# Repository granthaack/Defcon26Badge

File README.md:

# Defcon26Badge

************************************************
Read the wiki!
https://github.com/granthaack/Defcon26Badge/wiki
************************************************

This is a custom badge for our friend group. At its core, it's an Atmel ATMEGA328P running the arduino bootloader. 

Peripherals:

-5x10 RGB Neopixel array

-LISDH Triple Axis Accelerometer

-NRF24L01 2.4GHz wireless transciever

-Piezo Buzzer

-6 Tact Switches

-3 Status Lights

-UART Debugging Port

The chip is soldered to the board, so it's programmed using an Arduino as an ISP. This also enables easy access to UART.

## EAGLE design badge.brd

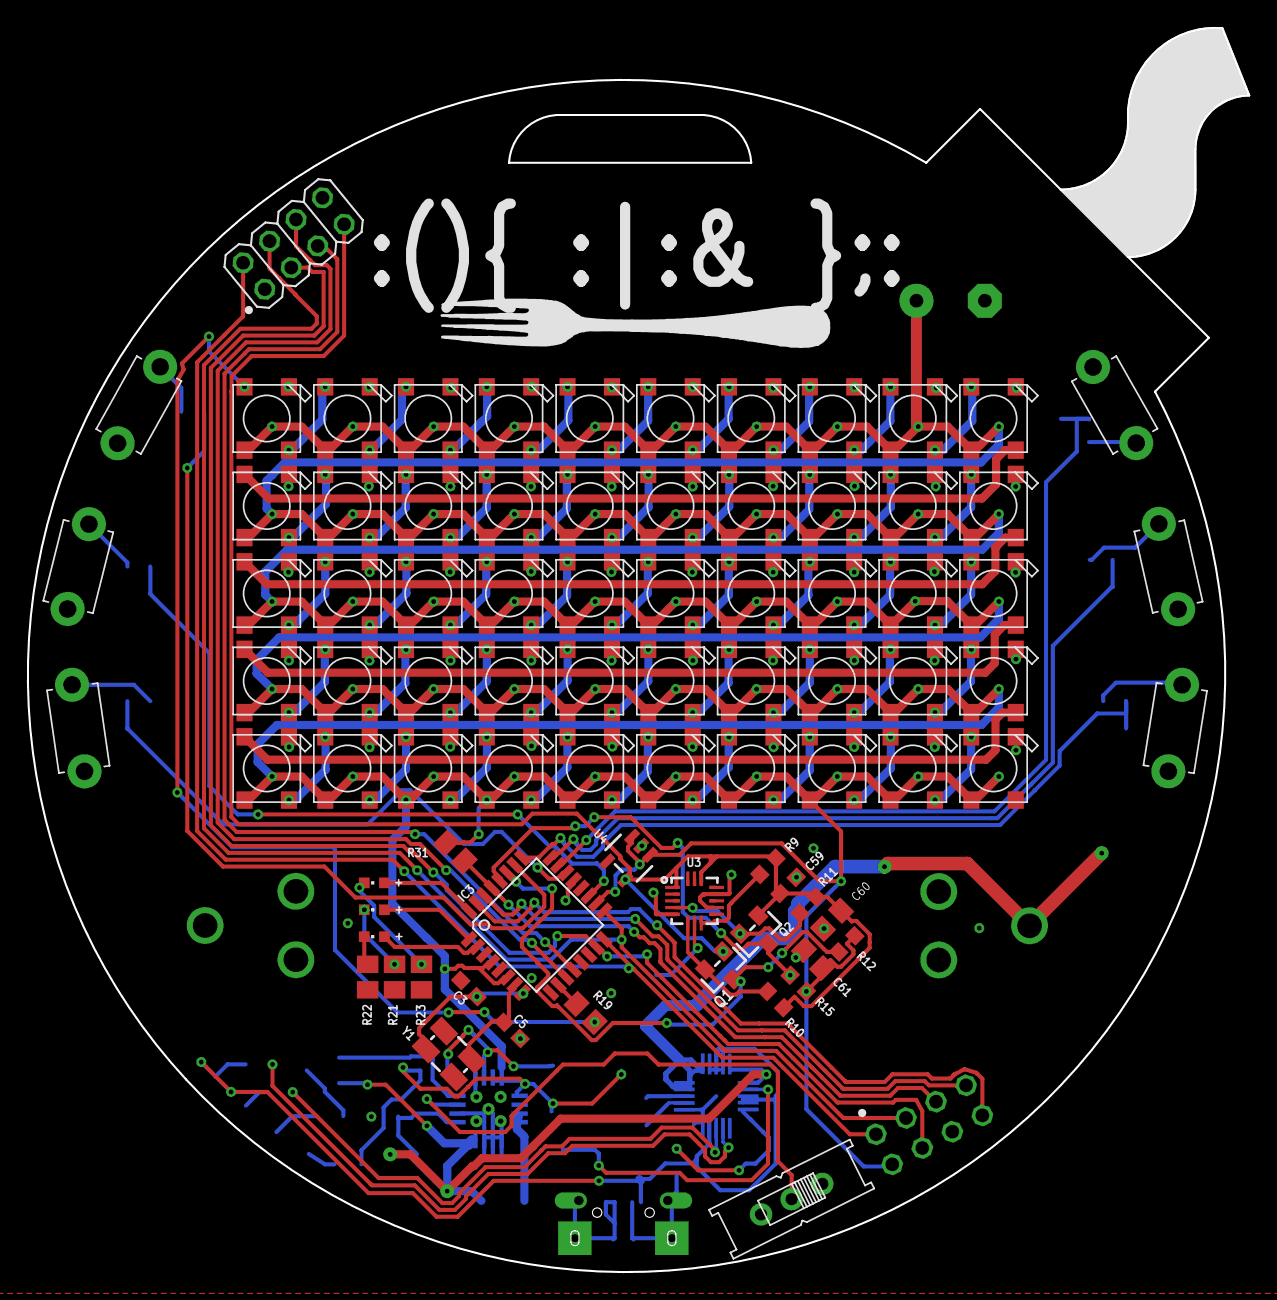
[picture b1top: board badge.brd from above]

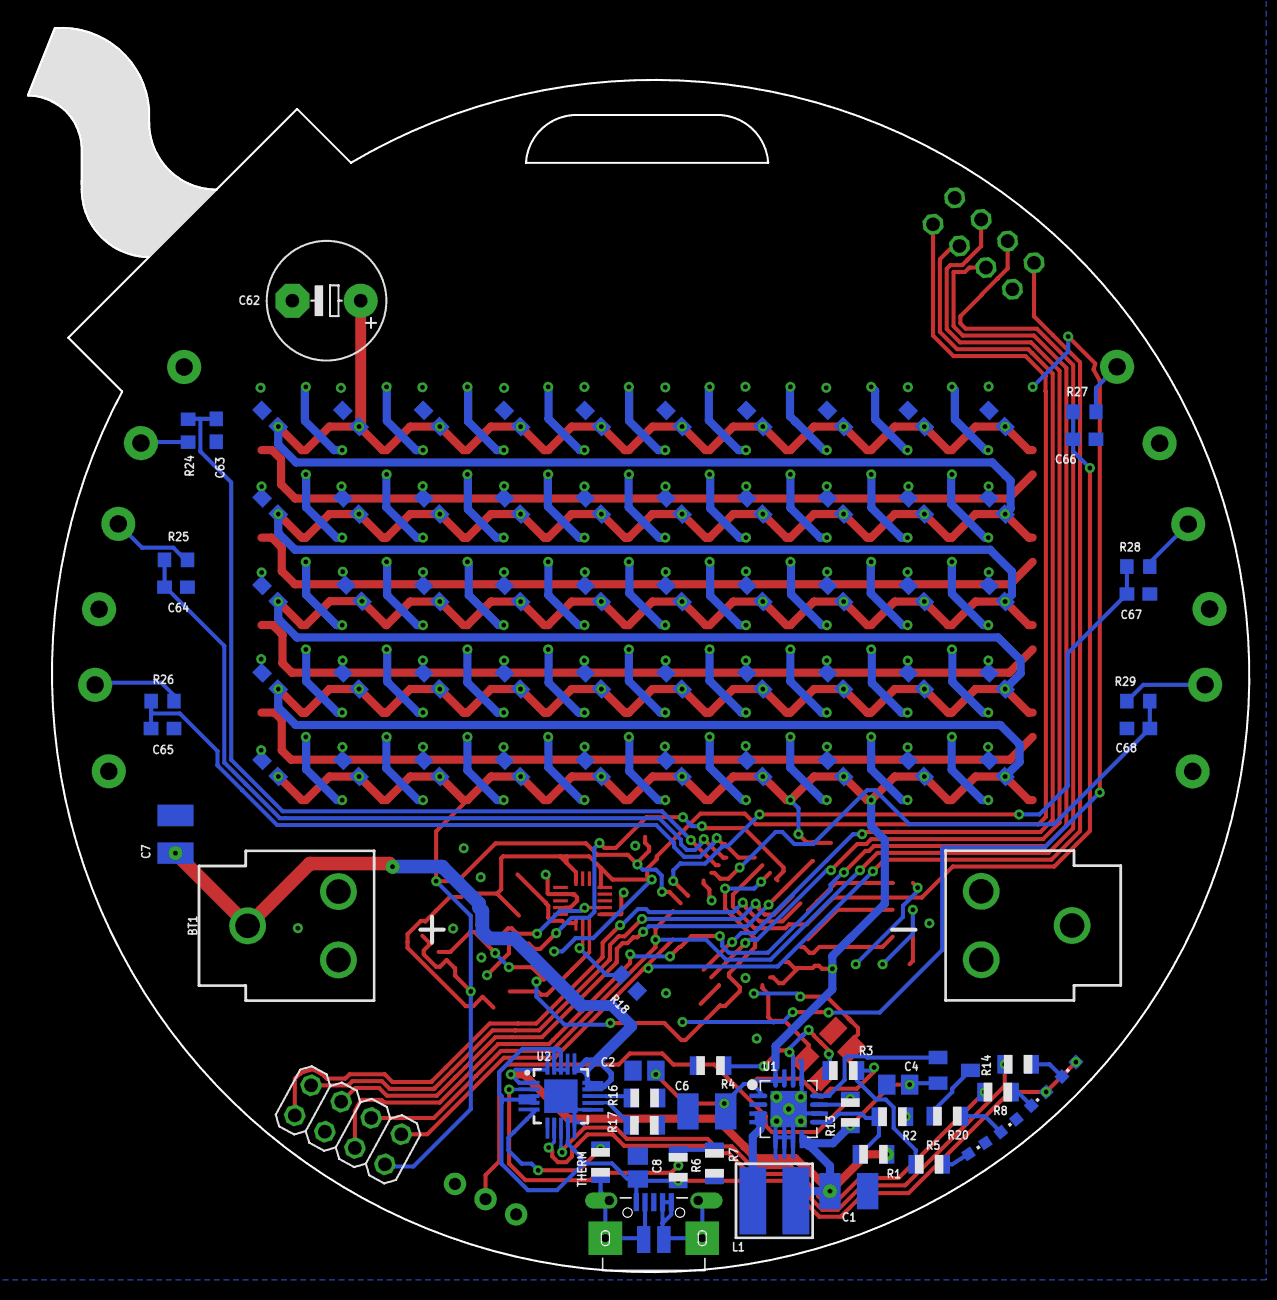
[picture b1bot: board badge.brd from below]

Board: 2 copper layers, 90.7 x 92.4 mm, 177 parts (95 on the bottom side), 107 nets.

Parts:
BT1: BATTERY_18650-HOLDER
C1, C7: 10uF; C1210
C2: 2.2uF; C0805
C3, C5: 22pF; C0603
C4: 0.1uF; C0805
C6: 100uF; C1210
C8: 10uf; C0805
C9, C10, C11, C12, C13, C14, C15, C16, C17, C18, C19, C20, C21, C22, C23, C24, C25, C26, C27, C28, C29, C30, C31, C32, C33, C34, C35, C36, C37, C38, C39, C40, C41, C42, C43, C44, C45, C46, C47, C48, C49, C50, C51, C52, C53, C54, C55, C56, C57, C58, C63, C64, C65, C66, C67, C68: 100nF; C0603
C59: 0.1uF; C0603
C60, C61: 10µF; C0805
C62: 1F; E5-8,5
CHRG/LBO: ORANGE; ADAFRUIT_CHIPLED_0603
CN4: MicroUSB; 4UCONN_20329
DONE: GREEN; ADAFRUIT_CHIPLED_0603
IC3: MEGA8-AI; TQFP32-08
JP1: PROG_HEADER; 2X04
JP3: TCVR_HEADER; 2X04
L1: 6.8uH; INDUCTOR_5X5MM_TDK_VLC5045
LBO: RED; ADAFRUIT_CHIPLED_0603
LED1, LED2, LED3, LED4, LED5, LED6, LED7, LED8, LED9, LED10, LED11, LED12, LED13, LED14, LED15, LED16, LED17, LED18, LED19, LED20, LED21, LED22, LED23, LED24, LED25, LED26, LED27, LED28, LED29, LED30, LED31, LED32, LED33, LED34, LED35, LED36, LED37, LED38, LED39, LED40, LED41, LED42, LED43, LED44, LED45, LED46, LED47, LED48, LED49, LED50: WS2812B5050-NARROW; WS2812B-NARROW
ON: BLUE; ADAFRUIT_CHIPLED_0603
Q1, Q2: BSS138; SOT23-WIDE
R1, R3: 1.87M; R0805
R2: 340K; R0805
R4, R13: 200K; R0805
R5, R8, R14, R20: 1K; R0805
R6: 270K; R0805
R7, R17: 100K; R0805
R9, R10, R11, R12, R15, R18: 10K; R0603
R16: 1.0K; R0805
R19: 470; R0805
R21, R22, R23: 220; M0805
R24, R25, R26, R27, R28, R29: 1k; R0603
R31: 10k; M0805
S1: EG1218
STAT1, STAT2, STAT3: GREEN; ADAFRUIT_CHIPLED_0603
SW1, SW2, SW3, SW4, SW5, SW6: TACT_PANA-EVQ
T1: MMUN2133LT1G; TRANSISTOR_SC59-BEC
THERM: 15K; R0805
U1: TPS61090RSAR; PVQFN-16
U2: MCP73871; QFN20_4MM
U3: LIS3DHTR; LGA16_3X3MM
U4: MIC5225-3.3; SOT23-5
Y1: 16.00MHz; CRYSTAL-SMD-3.2X2.5MM

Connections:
3.3V: C59.1, C60.1, JP3.7, Q1.1, Q2.1, R9.1, R10.2, R11.2, U3.1, U3.14, U4.5
+5V: C2.1, C6.1, C9.1, C10.1, C11.1, C12.1, C13.1, C14.1, C15.1, C16.1, C17.1, C18.1, C19.1, C20.1, C21.1, C22.1, C23.1, C24.1, C25.1, C26.1, C27.1, C28.1, C29.1, C30.1, C31.1, C32.1, C33.1, C34.1, C35.1, C36.1, C37.1, C38.1, C39.1, C40.1, C41.1, C42.1, C43.1, C44.1, C45.1, C46.1, C47.1, C48.1, C49.1, C50.1, C51.1, C52.1, C53.1, C54.1, C55.1, C56.1, C57.1, C58.1, C61.1, C62.+, IC3.4, IC3.6, IC3.18, JP1.2, LED1.1-VDD, LED2.1-VDD, LED3.1-VDD, LED4.1-VDD, LED5.1-VDD, LED6.1-VDD, LED7.1-VDD, LED8.1-VDD, LED9.1-VDD, LED10.1-VDD, LED11.1-VDD, LED12.1-VDD, LED13.1-VDD, LED14.1-VDD, LED15.1-VDD, LED16.1-VDD, LED17.1-VDD, LED18.1-VDD, LED19.1-VDD, LED20.1-VDD, LED21.1-VDD, LED22.1-VDD, LED23.1-VDD, LED24.1-VDD, LED25.1-VDD, LED26.1-VDD, LED27.1-VDD, LED28.1-VDD, LED29.1-VDD, LED30.1-VDD, LED31.1-VDD, LED32.1-VDD, LED33.1-VDD, LED34.1-VDD, LED35.1-VDD, LED36.1-VDD, LED37.1-VDD, LED38.1-VDD, LED39.1-VDD, LED40.1-VDD, LED41.1-VDD, LED42.1-VDD, LED43.1-VDD, LED44.1-VDD, LED45.1-VDD, LED46.1-VDD, LED47.1-VDD, LED48.1-VDD, LED49.1-VDD, LED50.1-VDD, R3.2, R5.1, R12.2, R15.2, R31.2, U1.1, U1.15, U1.16, U4.1, U4.3
BOOST_ENABLE: R13.2, S1.P, U1.11
CE: IC3.11, JP3.6
CSN: IC3.12, JP3.5
GND: BT1.GND@1, C1.2, C2.2, C3.2, C4.2, C5.2, C6.2, C7.2, C8.2, C9.2, C10.2, C11.2, C12.2, C13.2, C14.2, C15.2, C16.2, C17.2, C18.2, C19.2, C20.2, C21.2, C22.2, C23.2, C24.2, C25.2, C26.2, C27.2, C28.2, C29.2, C30.2, C31.2, C32.2, C33.2, C34.2, C35.2, C36.2, C37.2, C38.2, C39.2, C40.2, C41.2, C42.2, C43.2, C44.2, C45.2, C46.2, C47.2, C48.2, C49.2, C50.2, C51.2, C52.2, C53.2, C54.2, C55.2, C56.2, C57.2, C58.2, C59.2, C60.2, C61.2, C62.-, C63.2, C64.2, C65.2, C66.2, C67.2, C68.2, CN4.BASE@1, CN4.BASE@2, CN4.D+, CN4.D-, CN4.GND, CN4.ID, CN4.SPRT@1, CN4.SPRT@2, CN4.SPRT@3, CN4.SPRT@4, IC3.3, IC3.5, IC3.21, JP1.6, JP3.8, LBO.C, LED1.3-GND, LED2.3-GND, LED3.3-GND, LED4.3-GND, LED5.3-GND, LED6.3-GND, LED7.3-GND, LED8.3-GND, LED9.3-GND, LED10.3-GND, LED11.3-GND, LED12.3-GND, LED13.3-GND, LED14.3-GND, LED15.3-GND, LED16.3-GND, LED17.3-GND, LED18.3-GND, LED19.3-GND, LED20.3-GND, LED21.3-GND, LED22.3-GND, LED23.3-GND, LED24.3-GND, LED25.3-GND, LED26.3-GND, LED27.3-GND, LED28.3-GND, LED29.3-GND, LED30.3-GND, LED31.3-GND, LED32.3-GND, LED33.3-GND, LED34.3-GND, LED35.3-GND, LED36.3-GND, LED37.3-GND, LED38.3-GND, LED39.3-GND, LED40.3-GND, LED41.3-GND, LED42.3-GND, LED43.3-GND, LED44.3-GND, LED45.3-GND, LED46.3-GND, LED47.3-GND, LED48.3-GND, LED49.3-GND, LED50.3-GND, ON.C, R2.1, R4.1, R7.2, R16.1, R17.1, R18.1, R21.1, R22.1, R23.1, S1.S, SW1.P$1, SW2.P$1, SW3.P$1, SW4.P$1, SW5.P$1, SW6.P$1, THERM.1, U1.5, U1.6, U1.7, U1.10, U1.13, U1.P$18, U1.P$19, U1.P$20, U1.P$21, U1.P$22, U1.THERMAL, U2.P$10, U2.P$11, U2.P$21, U3.5, U3.10, U3.12, U4.2
LBO: T1.B, U1.12
MISO: IC3.16, JP1.1, JP3.2
MOSI: IC3.15, JP1.4, JP3.3
unnamed: L1.P$2, U1.3, U1.4
unnamed: LBO.A, R20.1
unnamed: R1.1, R2.2, U1.9
unnamed: ON.A, R5.2
unnamed: R3.1, R4.2, U1.14
unnamed: R20.2, T1.C
unnamed: R6.1, R7.1, U2.P$2
unnamed: DONE.C, R14.2
unnamed: R14.1, U2.P$7
unnamed: THERM.2, U2.P$5
unnamed: R8.1, U2.P$8
unnamed: CHRG/LBO.C, R8.2
unnamed: R17.2, U2.P$12
unnamed: C5.1, IC3.7, Y1.3
unnamed: C3.1, IC3.8, Y1.1
unnamed: R16.2, U2.P$13
unnamed: LED2.2-DOUT, LED3.4-DIN
unnamed: R9.2, U3.8
unnamed: R21.2, STAT2.C
unnamed: R22.2, STAT3.C
unnamed: R23.2, STAT1.C
unnamed: R24.2, SW1.P$2
unnamed: LED1.2-DOUT, LED2.4-DIN
unnamed: LED3.2-DOUT, LED4.4-DIN
unnamed: LED4.2-DOUT, LED5.4-DIN
unnamed: LED5.2-DOUT, LED6.4-DIN
unnamed: R26.2, SW3.P$2
unnamed: R28.2, SW5.P$2
unnamed: R29.2, SW6.P$2
unnamed: R27.2, SW4.P$2
unnamed: R25.2, SW2.P$2
unnamed: LED6.2-DOUT, LED7.4-DIN
unnamed: LED7.2-DOUT, LED8.4-DIN
unnamed: LED8.2-DOUT, LED9.4-DIN
unnamed: LED9.2-DOUT, LED10.4-DIN
unnamed: LED10.2-DOUT, LED11.4-DIN
unnamed: LED11.2-DOUT, LED12.4-DIN
unnamed: LED12.2-DOUT, LED13.4-DIN
unnamed: LED13.2-DOUT, LED14.4-DIN
unnamed: LED14.2-DOUT, LED15.4-DIN
unnamed: LED15.2-DOUT, LED16.4-DIN
unnamed: LED16.2-DOUT, LED17.4-DIN
unnamed: LED17.2-DOUT, LED18.4-DIN
unnamed: LED18.2-DOUT, LED19.4-DIN
unnamed: LED19.2-DOUT, LED20.4-DIN
unnamed: LED20.2-DOUT, LED21.4-DIN
unnamed: LED21.2-DOUT, LED22.4-DIN
unnamed: LED22.2-DOUT, LED23.4-DIN
unnamed: LED23.2-DOUT, LED24.4-DIN
unnamed: LED24.2-DOUT, LED25.4-DIN
unnamed: LED25.2-DOUT, LED26.4-DIN
unnamed: LED26.2-DOUT, LED27.4-DIN
unnamed: LED27.2-DOUT, LED28.4-DIN
unnamed: LED28.2-DOUT, LED29.4-DIN
unnamed: LED29.2-DOUT, LED30.4-DIN
unnamed: LED30.2-DOUT, LED31.4-DIN
unnamed: LED31.2-DOUT, LED32.4-DIN
unnamed: LED32.2-DOUT, LED33.4-DIN
unnamed: LED33.2-DOUT, LED34.4-DIN
unnamed: LED34.2-DOUT, LED35.4-DIN
unnamed: LED35.2-DOUT, LED36.4-DIN
unnamed: LED36.2-DOUT, LED37.4-DIN
unnamed: LED37.2-DOUT, LED38.4-DIN
unnamed: LED38.2-DOUT, LED39.4-DIN
unnamed: LED39.2-DOUT, LED40.4-DIN
unnamed: LED40.2-DOUT, LED41.4-DIN
unnamed: LED41.2-DOUT, LED42.4-DIN
unnamed: LED42.2-DOUT, LED43.4-DIN
unnamed: LED43.2-DOUT, LED44.4-DIN
unnamed: LED44.2-DOUT, LED45.4-DIN
unnamed: LED45.2-DOUT, LED46.4-DIN
unnamed: LED46.2-DOUT, LED47.4-DIN
unnamed: LED47.2-DOUT, LED48.4-DIN
unnamed: LED48.2-DOUT, LED49.4-DIN
unnamed: LED49.2-DOUT, LED50.4-DIN
NEO-DOUT: IC3.10, R19.1
PIXEL_DATA: LED1.4-DIN, R19.2
RESET_PROG: IC3.29, JP1.5, R31.1
RX: IC3.30, JP1.7
SCK: IC3.17, JP1.3, JP3.4
SCL: IC3.28, Q2.3, R15.1
SCL_3.3V: Q2.2, R11.1, U3.4
SDA: IC3.27, Q1.3, R12.1
SDA_3.3V: Q1.2, R10.1, U3.6
SDO: R18.2, U3.7
STAT1: IC3.32, STAT1.A
STAT2: IC3.1, STAT2.A
STAT3: IC3.2, STAT3.A
SW1: C63.1, IC3.23, R24.1
SW2: C64.1, IC3.24, R25.1
SW3: C65.1, IC3.25, R26.1
SW4: C66.1, IC3.26, R27.1
SW5: C67.1, IC3.19, R28.1
SW6: C68.1, IC3.22, R29.1
TX: IC3.31, JP1.8
VBAT: C1.1, C4.1, L1.P$1, R1.2, R13.1, T1.E, U1.8, U2.P$1, U2.P$20
VBUS: C8.1, CHRG/LBO.A, CN4.VBUS, DONE.A, R6.2, U2.P$3, U2.P$4, U2.P$9, U2.P$17, U2.P$18, U2.P$19
VLIPO: BT1.PWR@1, C7.1, U2.P$14, U2.P$15, U2.P$16

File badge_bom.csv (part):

On Digikey,Part,Value,Device,Package,Description,MF,MPN,OC_FARNELL,OC_NEWARK,PROD_ID,SF_SKU
x,BT1,,BATTERY-18650,BATTERY_18650-HOLDER,Battery - Single Cell,,,,,BATT-12327,PRT-13113
x,C1,10uF,C-USC1210,C1210,"CAPACITOR, American symbol",,,,,,
x,C2,2.2uF,C-USC0805,C0805,"CAPACITOR, American symbol",,,,,,
x,C3,22pF,C-USC0603,C0603,"CAPACITOR, American symbol",,,,,,
x,C4,0.1uF,C-USC0805,C0805,"CAPACITOR, American symbol",,,,,,
x,C5,22pF,C-USC0603,C0603,"CAPACITOR, American symbol",,,,,,
x,C6,100uF,C-USC1210,C1210,"CAPACITOR, American symbol",,,,,,
x,C7,10uF,C-USC1210,C1210,"CAPACITOR, American symbol",,,,,,
x,C8,10uf,C-USC0805,C0805,"CAPACITOR, American symbol",,,,,,
x,C9,100nF,C-USC0603,C0603,"CAPACITOR, American symbol",,,,,,
x,C10,100nF,C-USC0603,C0603,"CAPACITOR, American symbol",,,,,,
x,C11,100nF,C-USC0603,C0603,"CAPACITOR, American symbol",,,,,,
x,C12,100nF,C-USC0603,C0603,"CAPACITOR, American symbol",,,,,,
x,C13,100nF,C-USC0603,C0603,"CAPACITOR, American symbol",,,,,,
x,C14,100nF,C-USC0603,C0603,"CAPACITOR, American symbol",,,,,,
x,C15,100nF,C-USC0603,C0603,"CAPACITOR, American symbol",,,,,,
x,C16,100nF,C-USC0603,C0603,"CAPACITOR, American symbol",,,,,,
x,C17,100nF,C-USC0603,C0603,"CAPACITOR, American symbol",,,,,,
x,C18,100nF,C-USC0603,C0603,"CAPACITOR, American symbol",,,,,,
x,C19,100nF,C-USC0603,C0603,"CAPACITOR, American symbol",,,,,,
x,C20,100nF,C-USC0603,C0603,"CAPACITOR, American symbol",,,,,,
x,C21,100nF,C-USC0603,C0603,"CAPACITOR, American symbol",,,,,,
x,C22,100nF,C-USC0603,C0603,"CAPACITOR, American symbol",,,,,,
x,C23,100nF,C-USC0603,C0603,"CAPACITOR, American symbol",,,,,,
x,C24,100nF,C-USC0603,C0603,"CAPACITOR, American symbol",,,,,,
x,C25,100nF,C-USC0603,C0603,"CAPACITOR, American symbol",,,,,,
x,C26,100nF,C-USC0603,C0603,"CAPACITOR, American symbol",,,,,,
x,C27,100nF,C-USC0603,C0603,"CAPACITOR, American symbol",,,,,,
x,C28,100nF,C-USC0603,C0603,"CAPACITOR, American symbol",,,,,,
x,C29,100nF,C-USC0603,C0603,"CAPACITOR, American symbol",,,,,,
x,C30,100nF,C-USC0603,C0603,"CAPACITOR, American symbol",,,,,,
x,C31,100nF,C-USC0603,C0603,"CAPACITOR, American symbol",,,,,,
x,C32,100nF,C-USC0603,C0603,"CAPACITOR, American symbol",,,,,,
x,C33,100nF,C-USC0603,C0603,"CAPACITOR, American symbol",,,,,,
x,C34,100nF,C-USC0603,C0603,"CAPACITOR, American symbol",,,,,,
x,C35,100nF,C-USC0603,C0603,"CAPACITOR, American symbol",,,,,,
x,C36,100nF,C-USC0603,C0603,"CAPACITOR, American symbol",,,,,,
x,C37,100nF,C-USC0603,C0603,"CAPACITOR, American symbol",,,,,,
x,C38,100nF,C-USC0603,C0603,"CAPACITOR, American symbol",,,,,,
x,C39,100nF,C-USC0603,C0603,"CAPACITOR, American symbol",,,,,,
x,C40,100nF,C-USC0603,C0603,"CAPACITOR, American symbol",,,,,,
x,C41,100nF,C-USC0603,C0603,"CAPACITOR, American symbol",,,,,,
x,C42,100nF,C-USC0603,C0603,"CAPACITOR, American symbol",,,,,,
x,C43,100nF,C-USC0603,C0603,"CAPACITOR, American symbol",,,,,,
x,C44,100nF,C-USC0603,C0603,"CAPACITOR, American symbol",,,,,,
x,C45,100nF,C-USC0603,C0603,"CAPACITOR, American symbol",,,,,,
x,C46,100nF,C-USC0603,C0603,"CAPACITOR, American symbol",,,,,,
x,C47,100nF,C-USC0603,C0603,"CAPACITOR, American symbol",,,,,,
x,C48,100nF,C-USC0603,C0603,"CAPACITOR, American symbol",,,,,,
x,C49,100nF,C-USC0603,C0603,"CAPACITOR, American symbol",,,,,,
x,C50,100nF,C-USC0603,C0603,"CAPACITOR, American symbol",,,,,,
x,C51,100nF,C-USC0603,C0603,"CAPACITOR, American symbol",,,,,,
x,C52,100nF,C-USC0603,C0603,"CAPACITOR, American symbol",,,,,,
x,C53,100nF,C-USC0603,C0603,"CAPACITOR, American symbol",,,,,,
x,C54,100nF,C-USC0603,C0603,"CAPACITOR, American symbol",,,,,,
x,C55,100nF,C-USC0603,C0603,"CAPACITOR, American symbol",,,,,,
x,C56,100nF,C-USC0603,C0603,"CAPACITOR, American symbol",,,,,,
x,C57,100nF,C-USC0603,C0603,"CAPACITOR, American symbol",,,,,,
x,C58,100nF,C-USC0603,C0603,"CAPACITOR, American symbol",,,,,,
x,C59,0.1uF,C-USC0603,C0603,"CAPACITOR, American symbol",,,,,,
x,C60,10µF,C-USC0805,C0805,"CAPACITOR, American symbol",,,,,,
x,C61,10µF,C-USC0805,C0805,"CAPACITOR, American symbol",,,,,,
x,C62,1F,CPOL-USE5-8.5,"E5-8,5","POLARIZED CAPACITOR, American symbol",,,,,,
x,C63,100nF,C-USC0603,C0603,"CAPACITOR, American symbol",,,,,,
x,C64,100nF,C-USC0603,C0603,"CAPACITOR, American symbol",,,,,,
x,C65,100nF,C-USC0603,C0603,"CAPACITOR, American symbol",,,,,,
x,C66,100nF,C-USC0603,C0603,"CAPACITOR, American symbol",,,,,,
x,C67,100nF,C-USC0603,C0603,"CAPACITOR, American symbol",,,,,,
x,C68,100nF,C-USC0603,C0603,"CAPACITOR, American symbol",,,,,,
x,CHRG/LBO,ORANGE,ADAFRUIT_LEDCHIPLED_0603,ADAFRUIT_CHIPLED_0603,LED,,,,,,
x,CN4,MicroUSB,USBMICRO_20329,4UCONN_20329,USB Connectors,,,,,,
x,DONE,GREEN,ADAFRUIT_LEDCHIPLED_0603,ADAFRUIT_CHIPLED_0603,LED,,,,,,
x,IC3,MEGA8-AI,MEGA8-AI,TQFP32-08,MICROCONTROLLER,,ATMEGA8-16AU,9171371,73M8863,,
x,JP1,PROG_HEADER,PINHD-2X4,2X04,PIN HEADER,,,,,,
x,JP3,TCVR_HEADER,PINHD-2X4,2X04,PIN HEADER,,,,,,
,L1,6.8uH,INDUCTORTDK_VLC5045,INDUCTOR_5X5MM_TDK_VLC5045,Inductors,,,,,,
,LBO,RED,ADAFRUIT_LEDCHIPLED_0603,ADAFRUIT_CHIPLED_0603,LED,,,,,,
x,LED1,WS2812B5050-NARROW,WS2812B5050-NARROW,WS2812B-NARROW,,,,,,,
x,LED2,WS2812B5050-NARROW,WS2812B5050-NARROW,WS2812B-NARROW,,,,,,,
x,LED3,WS2812B5050-NARROW,WS2812B5050-NARROW,WS2812B-NARROW,,,,,,,
x,LED4,WS2812B5050-NARROW,WS2812B5050-NARROW,WS2812B-NARROW,,,,,,,
x,LED5,WS2812B5050-NARROW,WS2812B5050-NARROW,WS2812B-NARROW,,,,,,,
x,LED6,WS2812B5050-NARROW,WS2812B5050-NARROW,WS2812B-NARROW,,,,,,,
x,LED7,WS2812B5050-NARROW,WS2812B5050-NARROW,WS2812B-NARROW,,,,,,,
x,LED8,WS2812B5050-NARROW,WS2812B5050-NARROW,WS2812B-NARROW,,,,,,,
x,LED9,WS2812B5050-NARROW,WS2812B5050-NARROW,WS2812B-NARROW,,,,,,,
x,LED10,WS2812B5050-NARROW,WS2812B5050-NARROW,WS2812B-NARROW,,,,,,,
x,LED11,WS2812B5050-NARROW,WS2812B5050-NARROW,WS2812B-NARROW,,,,,,,
x,LED12,WS2812B5050-NARROW,WS2812B5050-NARROW,WS2812B-NARROW,,,,,,,
x,LED13,WS2812B5050-NARROW,WS2812B5050-NARROW,WS2812B-NARROW,,,,,,,
x,LED14,WS2812B5050-NARROW,WS2812B5050-NARROW,WS2812B-NARROW,,,,,,,
x,LED15,WS2812B5050-NARROW,WS2812B5050-NARROW,WS2812B-NARROW,,,,,,,
x,LED16,WS2812B5050-NARROW,WS2812B5050-NARROW,WS2812B-NARROW,,,,,,,
x,LED17,WS2812B5050-NARROW,WS2812B5050-NARROW,WS2812B-NARROW,,,,,,,
x,LED18,WS2812B5050-NARROW,WS2812B5050-NARROW,WS2812B-NARROW,,,,,,,
x,LED19,WS2812B5050-NARROW,WS2812B5050-NARROW,WS2812B-NARROW,,,,,,,
x,LED20,WS2812B5050-NARROW,WS2812B5050-NARROW,WS2812B-NARROW,,,,,,,
x,LED21,WS2812B5050-NARROW,WS2812B5050-NARROW,WS2812B-NARROW,,,,,,,
x,LED22,WS2812B5050-NARROW,WS2812B5050-NARROW,WS2812B-NARROW,,,,,,,
x,LED23,WS2812B5050-NARROW,WS2812B5050-NARROW,WS2812B-NARROW,,,,,,,
x,LED24,WS2812B5050-NARROW,WS2812B5050-NARROW,WS2812B-NARROW,,,,,,,
x,LED25,WS2812B5050-NARROW,WS2812B5050-NARROW,WS2812B-NARROW,,,,,,,
x,LED26,WS2812B5050-NARROW,WS2812B5050-NARROW,WS2812B-NARROW,,,,,,,
x,LED27,WS2812B5050-NARROW,WS2812B5050-NARROW,WS2812B-NARROW,,,,,,,
x,LED28,WS2812B5050-NARROW,WS2812B5050-NARROW,WS2812B-NARROW,,,,,,,
x,LED29,WS2812B5050-NARROW,WS2812B5050-NARROW,WS2812B-NARROW,,,,,,,
x,LED30,WS2812B5050-NARROW,WS2812B5050-NARROW,WS2812B-NARROW,,,,,,,
x,LED31,WS2812B5050-NARROW,WS2812B5050-NARROW,WS2812B-NARROW,,,,,,,
x,LED32,WS2812B5050-NARROW,WS2812B5050-NARROW,WS2812B-NARROW,,,,,,,
x,LED33,WS2812B5050-NARROW,WS2812B5050-NARROW,WS2812B-NARROW,,,,,,,
x,LED34,WS2812B5050-NARROW,WS2812B5050-NARROW,WS2812B-NARROW,,,,,,,
x,LED35,WS2812B5050-NARROW,WS2812B5050-NARROW,WS2812B-NARROW,,,,,,,
x,LED36,WS2812B5050-NARROW,WS2812B5050-NARROW,WS2812B-NARROW,,,,,,,
x,LED37,WS2812B5050-NARROW,WS2812B5050-NARROW,WS2812B-NARROW,,,,,,,
x,LED38,WS2812B5050-NARROW,WS2812B5050-NARROW,WS2812B-NARROW,,,,,,,
x,LED39,WS2812B5050-NARROW,WS2812B5050-NARROW,WS2812B-NARROW,,,,,,,
x,LED40,WS2812B5050-NARROW,WS2812B5050-NARROW,WS2812B-NARROW,,,,,,,
x,LED41,WS2812B5050-NARROW,WS2812B5050-NARROW,WS2812B-NARROW,,,,,,,
x,LED42,WS2812B5050-NARROW,WS2812B5050-NARROW,WS2812B-NARROW,,,,,,,
x,LED43,WS2812B5050-NARROW,WS2812B5050-NARROW,WS2812B-NARROW,,,,,,,
x,LED44,WS2812B5050-NARROW,WS2812B5050-NARROW,WS2812B-NARROW,,,,,,,
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
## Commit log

2018-06-03 Worked on badge shape
2018-06-04 Added power management circuitry and the MCU
2018-06-04 Cut down the LEDs to 50 and added filter caps for each
2018-06-04 Added accelerometer circuitry
2018-06-11 Added switches, status lights, RX/TX Headers
2018-06-13 -wired all the pixels -cleaned up the schematic
2018-06-13 haha forget to save fuck me
2018-06-13 small silkscreen changes
2018-06-18 Routed all the traces and performed a cursory DRC
2018-06-19 cleaned up the screenprinting
2018-06-20 generated a BOM and started to add parts to it on digikey
2018-06-23 cleaned up the traces and completed the BOM
2018-06-25 ready for production
2018-07-21 moved pcb files to a new folder
2018-07-21 moved readme
2018-07-21 initialized the arduino project
2018-07-21 Added general format for creation of display functions
2018-07-21 Created general layout for function locations Added struct and array for display function access
2018-07-21 Added Conway's Game of life to functions
2018-07-21 Added defcon26 scroll
2018-07-21 Fixed bugs and optimized
2018-07-21 Completed DefocnDraw
2018-07-21 added initialization of the accelerometer
2018-07-21 Changed mainupdate pointer to conway instead of defscroll
2018-07-22 built the accelerometer library
2018-07-22 made the accelerometer run on zero ram
2018-07-22 fixed a bug that never updated the y and z values
2018-07-22 wrote a custom pixel library that saves a whopping *2 bytes* of ram
2018-07-22 Create LICENSE
2018-07-22 fixed typos
2018-07-22 added a zipped simpix library for easy installation
2018-07-27 Added menuing and split up display file
2018-07-27 Added networking support for menu
2018-08-10 wrote quick prototype functions for updating the color of the circle and the radius of the circle
2018-08-11 Got the circle working

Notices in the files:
parts and their libraries:
microbuilder: This work is placed in the public domain, and may be freely used for commercial and non-commercial work with the following conditions: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
SparkFun-Batteries: Licensing: Creative Commons ShareAlike 4.0 International - https://creativecommons.org/licenses/by-sa/4.0
